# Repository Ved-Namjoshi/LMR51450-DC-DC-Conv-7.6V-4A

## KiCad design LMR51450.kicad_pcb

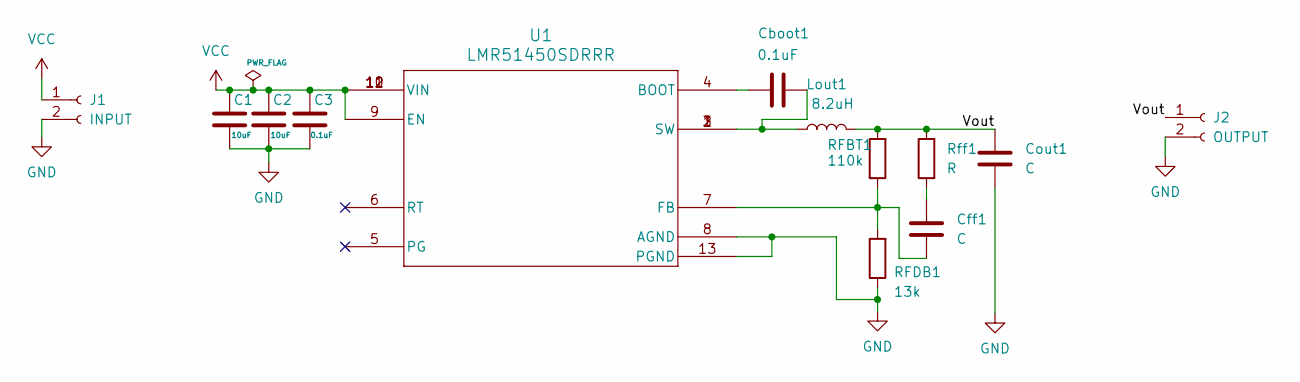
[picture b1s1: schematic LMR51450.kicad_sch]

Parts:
C1, C2: 10uF; C_0805_2012Metric_Pad1.18x1.45mm_HandSolder
C3: 0.1uF; C_0805_2012Metric_Pad1.18x1.45mm_HandSolder
Cboot1: 0.1uF; C_0805_2012Metric_Pad1.18x1.45mm_HandSolder
Cff1: C; C_0805_2012Metric_Pad1.18x1.45mm_HandSolder
Cout1: C; C_1808_4520Metric_Pad1.72x2.30mm_HandSolder
J1: INPUT; TerminalBlock_Phoenix_MKDS-1,5-2-5.08_1x02_P5.08mm_Horizont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
J2: OUTPUT; TerminalBlock_Phoenix_MKDS-1,5-2-5.08_1x02_P5.08mm_Horizont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
Lout1: 8.2uH; L_Axial_L11.0mm_D4.5mm_P15.24mm_Horizontal_Fastron_MECC
RFBT1: 110k; R_0805_2012Metric_Pad1.20x1.40mm_HandSolder
RFDB1: 13k; R_0805_2012Metric_Pad1.20x1.40mm_HandSolder
Rff1: R; R_0805_2012Metric_Pad1.20x1.40mm_HandSolder
U1: LMR51450SDRRR; WSON_SDRRR_TEX

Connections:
/Vout: Cout1.2, J2.1, Lout1.2, RFBT1.2, Rff1.2
GND: C1.1, C2.1, C3.1, Cout1.1, J1.2, J2.2, RFDB1.1, U1.8 (AGND), U1.13 (PGND)
unnamed: Cboot1.2, Lout1.1, U1.1 (SW), U1.2 (SW), U1.3 (SW)
unnamed: Cff1.2, Rff1.1
unnamed: Cboot1.1, U1.4 (BOOT)
unnamed: Cff1.1, RFBT1.1, RFDB1.2, U1.7 (FB)
VCC: C1.2, C2.2, C3.2, J1.1, U1.9 (EN), U1.10 (VIN), U1.11 (VIN), U1.12 (VIN)

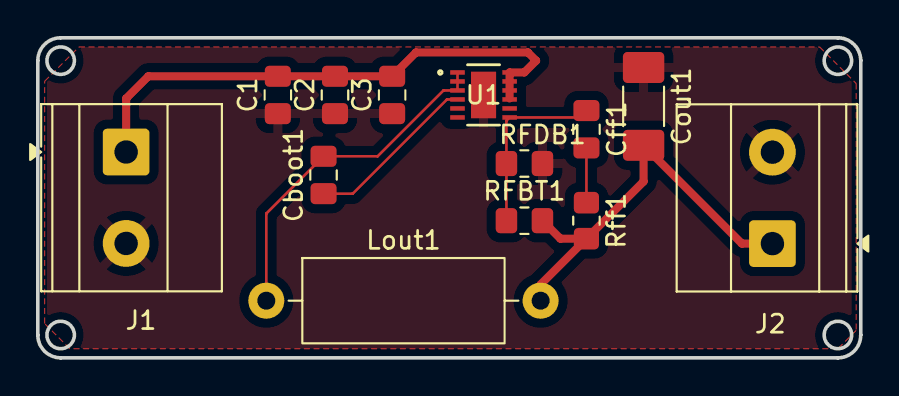
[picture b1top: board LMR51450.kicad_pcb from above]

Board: 2 copper layers, 45.7 x 17.8 mm, 13 parts (0 on the bottom side), 7 nets.

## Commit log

2025-09-10 Create Media
